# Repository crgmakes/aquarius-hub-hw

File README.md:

# Aquarius Hub Hardware

All the source files for the hub hardware.

# Software 

You will need [KiCad](https://kicad.org) to view and edit this design. Click [here](https://www.kicad.org/download/) to download.

You will also need all the associated libraries and models to drive the design if you want to make changes or view the 3D rendering:

https://github.com/crgmakes/kicad-library.git

Kicad MUST be configured properly to use all the files in this repo. Once you have Kicad installed, under Preferences->Configure Paths..., make the following entries:

1 - KICAD_USER_DIR -> set to the root location of where you placed the above repository.
2 - KICAD_USER_LIBRARY = ${KICAD_USER_DIR}/Library
3 - KICAD_USER_MODEL_DIR = ${KICAD_USER_LIBRARY}/models
4 - KICAD_USER_TEMPLATE_DIR	= ${KICAD_USER_LIBRARY}/templates	

Kicad will operate mostly normally if these are not set properly. You will notice an issue when you view the PCB in 3D mode.

***NOTE***: after makeing a release build in git, if your rendered 3D images are missing components, ensure the path to EVERY component model is set to ${KICAD_USER_MODEL_DIR}/<model name>.

Kicad sometimes replaces the variable with an expansion and that FAILS during the build process because the expanded variable is local and does not match the build environment.

---

THE DESIGN IS PROVIDED "AS IS" AND THE AUTHOR DISCLAIMS ALL WARRANTIES WITH REGARD TO THIS DESIGN INCLUDING ALL IMPLIED WARRANTIES OF MERCHANTABILITY AND FITNESS. IN NO EVENT SHALL THE AUTHOR BE LIABLE FOR ANY SPECIAL, DIRECT, INDIRECT, OR CONSEQUENTIAL DAMAGES OR ANY DAMAGES WHATSOEVER RESULTING FROM LOSS OF USE, DATA OR PROFITS, WHETHER IN AN ACTION OF CONTRACT, NEGLIGENCE OR OTHER TORTIOUS ACTION, ARISING OUT OF OR IN CONNECTION WITH THE USE OR PERFORMANCE OF THIS DESIGN.

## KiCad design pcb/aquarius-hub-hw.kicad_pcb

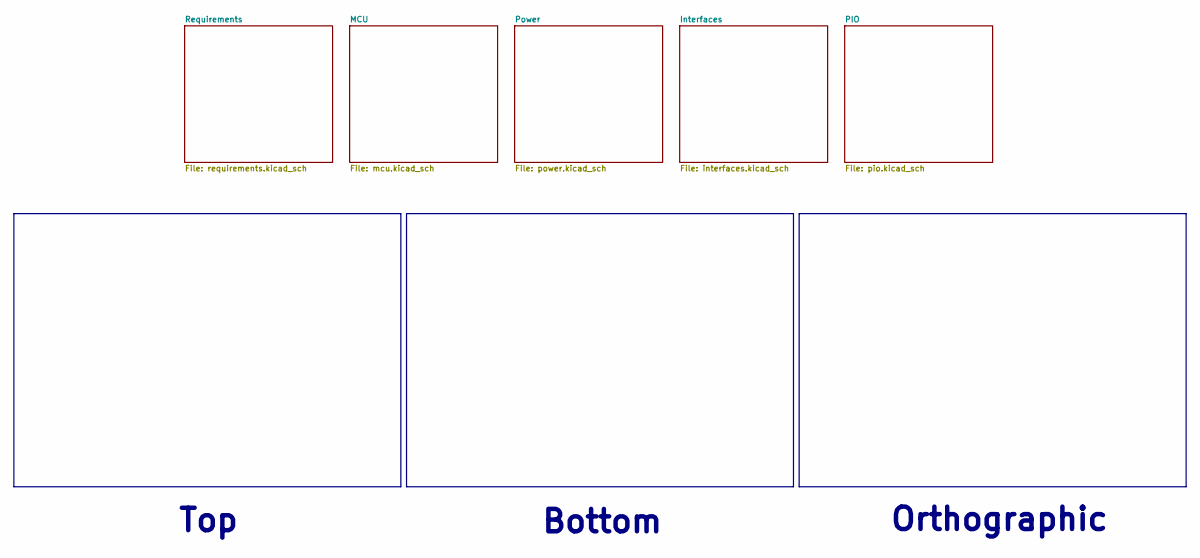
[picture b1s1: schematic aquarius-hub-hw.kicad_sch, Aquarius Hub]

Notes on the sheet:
Orthographic
Top
Bottom

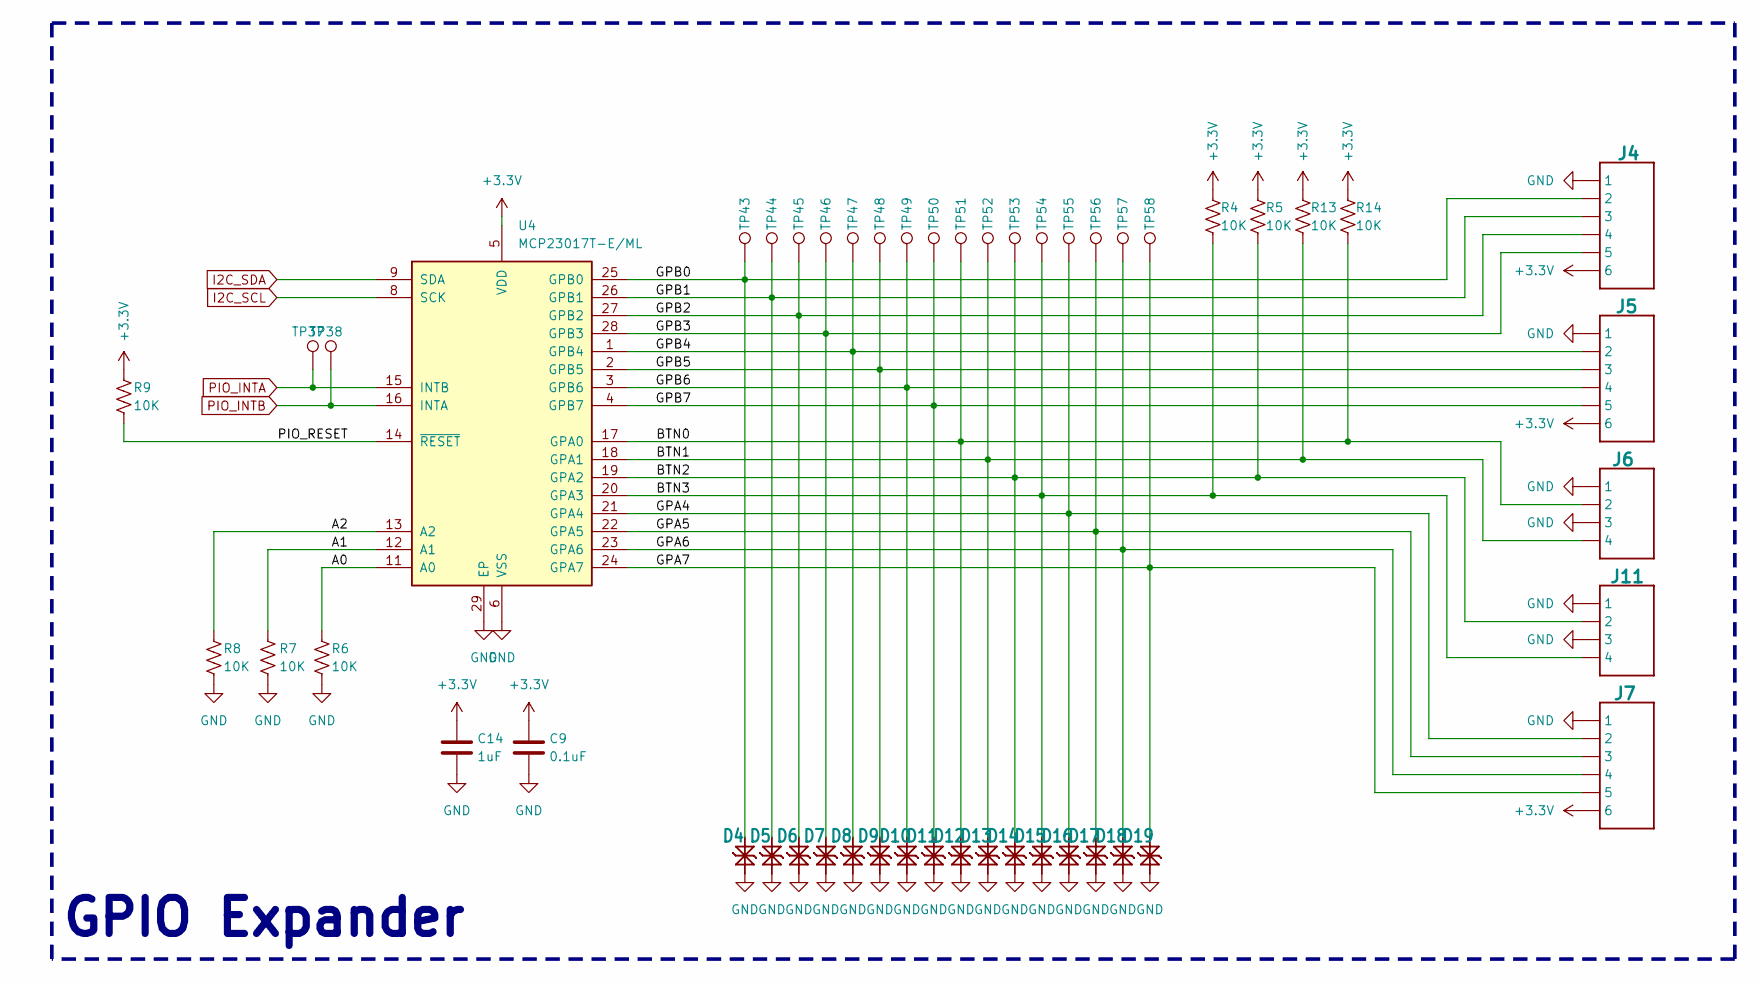
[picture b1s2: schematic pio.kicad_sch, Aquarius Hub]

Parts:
C9: 0.1uF; C_0603_1608Metric; MPN CL10B104KO8NNNC; LCSC C66501
C14: 1uF; C_0603_1608Metric; MPN CGA0603X5R105K160JT; LCSC C6119849
D4, D5, D6, D7, D8, D9, D10, D11, D12, D13, D14, D15, D16, D17, D18, D19: PESD3V3S1BL; DFN1006-2; MPN LESD8D3.3CAT5G; LCSC C5563754
J4, J5, J7: BM06B-SRSS-TB; JST_SH_BM06B-SRSS-TB_1x06-1MP_P1.00mm_Vertical; MPN BM06B-SRSS-TB; LCSC C2845374
J6, J11: BM04B-SRSS-TB; JST_SH_BM04B-SRSS-TB_1x04-1MP_P1.00mm_Vertical; MPN BM04B-SRSS-TBT(LF)(SN); Mouser 306-BM04BSRSSTBTLFSN
R4, R5, R6, R7, R8, R9, R13, R14: 10K; R_0603_1608Metric; MPN FRC0603J103TS; LCSC C2930027
TP37, TP38, TP43, TP44, TP45, TP46, TP47, TP48, TP49, TP50, TP51, TP52, TP53, TP54, TP55, TP56, TP57, TP58: TestPoint_Pad_D1.0mm
U4: MCP23017T-E/ML; QFN-28-1EP_6x6mm_P0.65mm_EP4.25x4.25mm; MPN MCP23017T-E/ML; LCSC C629439

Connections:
+3.3V: C9.1, C14.1, J4.6, J5.6, J7.6, R4.1, R5.1, R9.1, R13.1, R14.1, U4.5 (VDD); also elsewhere on the board
/PIO/A0: R6.1, U4.11 (A0)
/PIO/A1: R7.1, U4.12 (A1)
/PIO/A2: R8.1, U4.13 (A2)
/PIO/BTN0: D12.2 (K2), J6.2, R14.2, TP51.1, U4.17 (GPA0)
/PIO/BTN1: D13.2 (K2), J6.4, R13.2, TP52.1, U4.18 (GPA1)
/PIO/BTN2: D14.2 (K2), J11.2, R5.2, TP53.1, U4.19 (GPA2)
/PIO/BTN3: D15.2 (K2), J11.4, R4.2, TP54.1, U4.20 (GPA3)
/PIO/GPA4: D16.2 (K2), J7.2, TP55.1, U4.21 (GPA4)
/PIO/GPA5: D17.2 (K2), J7.3, TP56.1, U4.22 (GPA5)
/PIO/GPA6: D18.2 (K2), J7.4, TP57.1, U4.23 (GPA6)
/PIO/GPA7: D19.2 (K2), J7.5, TP58.1, U4.24 (GPA7)
/PIO/GPB0: D4.2 (K2), J4.2, TP43.1, U4.25 (GPB0)
/PIO/GPB1: D5.2 (K2), J4.3, TP44.1, U4.26 (GPB1)
/PIO/GPB2: D6.2 (K2), J4.4, TP45.1, U4.27 (GPB2)
/PIO/GPB3: D7.2 (K2), J4.5, TP46.1, U4.28 (GPB3)
/PIO/GPB4: D8.2 (K2), J5.2, TP47.1, U4.1 (GPB4)
/PIO/GPB5: D9.2 (K2), J5.3, TP48.1, U4.2 (GPB5)
/PIO/GPB6: D10.2 (K2), J5.4, TP49.1, U4.3 (GPB6)
/PIO/GPB7: D11.2 (K2), J5.5, TP50.1, U4.4 (GPB7)
/PIO/PIO_RESET: R9.2, U4.14 (~RESET)
GND: C9.2, C14.2, D4.1 (K1), D5.1 (K1), D6.1 (K1), D7.1 (K1), D8.1 (K1), D9.1 (K1), D10.1 (K1), D11.1 (K1), D12.1 (K1), D13.1 (K1), D14.1 (K1), D15.1 (K1), D16.1 (K1), D17.1 (K1), D18.1 (K1), D19.1 (K1), J4.1, J5.1, J6.1, J6.3, J7.1, J11.1, J11.3, R6.2, R7.2, R8.2, U4.6 (VSS), U4.29 (EP); also elsewhere on the board
I2C_SCL: U4.8 (SCK); also elsewhere on the board
I2C_SDA: U4.9 (SDA); also elsewhere on the board
PIO_INTA: TP37.1, U4.15 (INTB); also elsewhere on the board
PIO_INTB: TP38.1, U4.16 (INTA); also elsewhere on the board

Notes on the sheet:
GPIO Expander

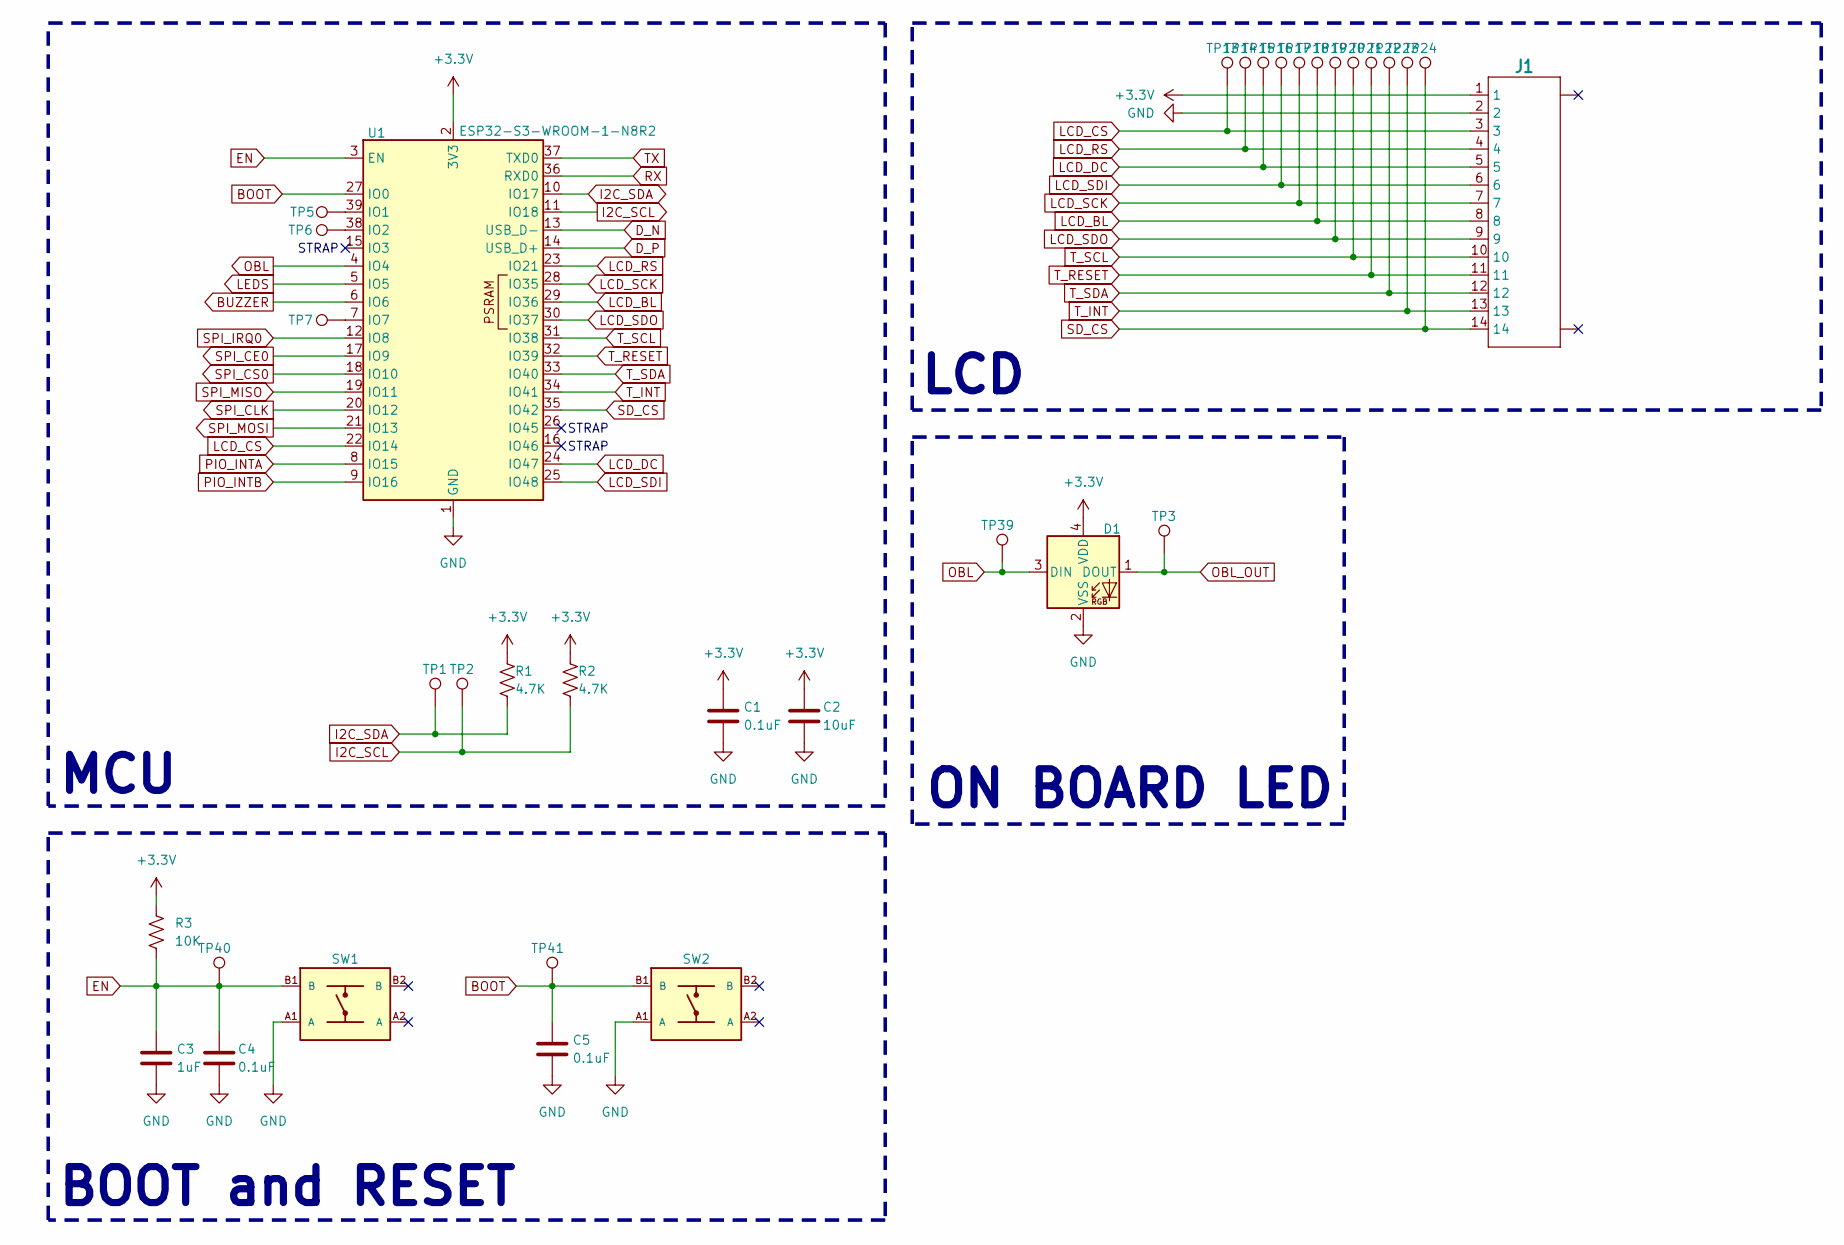
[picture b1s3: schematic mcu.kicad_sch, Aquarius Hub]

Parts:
C1, C4: 0.1uF; C_0603_1608Metric; MPN CL10B104KO8NNNC; Mouser 187-CL10B104KO8NNNC
C2: 10uF; C_0603_1608Metric; MPN CL10A106MO8NQNC; Mouser 187-CL10A106MO8NQNC
C3: 1uF; C_0603_1608Metric; Tolerance 10%; MPN CGA0603X5R105K160JT; Mouser 187-CL10B105KO8NNNC
C5: 0.1uF; C_0603_1608Metric; MPN CL10B104KO8NNNC; Digikey 1276-1005-2-ND
D1: WS2812B-2020; LED_WS2812B-2020_PLCC4_2.0x2.0mm; MPN WS2812C-2020-V1; LCSC C2976072
J1: XF2M-1415-1A; MPN XF2M-1415-1A; Mouser 653-XF2M-1415-1A
R1, R2: 4.7K; R_0603_1608Metric; MPN FRC0603J472 TS; Mouser 652-CR0603-JW-472ELF
R3: 10K; R_0603_1608Metric; MPN FRC0603J103TS; Mouser 652-CR0603-JW-103ELF
SW1, SW2: EVQ-Q2B02W; MPN EVQ-Q2B02W; Mouser 667-EVQ-Q2B02W
TP1, TP2, TP3, TP5, TP6, TP7, TP13, TP14, TP15, TP16, TP17, TP18, TP19, TP20, TP21, TP22, TP23, TP24, TP39, TP40, TP41: TestPoint_Pad_D1.0mm
U1: ESP32-S3-WROOM-1-N8R2; MPN ESP32-S3-WROOM-1-N8R2; Mouser 356-ESP32-S3WRM1N8R2

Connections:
+3.3V: C1.1, C2.1, D1.4 (VDD), J1.1, R1.1, R2.1, R3.1, U1.2 (3V3); also elsewhere on the board
BOOT: C5.1, SW2.B1 (B), TP41.1, U1.27 (IO0)
BUZZER: U1.6 (IO6); also elsewhere on the board
D_N: U1.13 (USB_D-); also elsewhere on the board
D_P: U1.14 (USB_D+); also elsewhere on the board
EN: C3.1, C4.1, R3.2, SW1.B1 (B), TP40.1, U1.3 (EN)
GND: C1.2, C2.2, C3.2, C4.2, C5.2, D1.2 (VSS), J1.2, SW1.A1 (A), SW2.A1 (A), U1.1 (GND), U1.40 (GND), U1.41 (GND); also elsewhere on the board
I2C_SCL: R2.2, TP2.1, U1.11 (IO18); also elsewhere on the board
I2C_SDA: R1.2, TP1.1, U1.10 (IO17); also elsewhere on the board
LCD_BL: J1.8, TP18.1, U1.29 (IO36)
LCD_CS: J1.3, TP13.1, U1.22 (IO14)
LCD_DC: J1.5, TP15.1, U1.24 (IO47)
LCD_RS: J1.4, TP14.1, U1.23 (IO21)
LCD_SCK: J1.7, TP17.1, U1.28 (IO35)
LCD_SDI: J1.6, TP16.1, U1.25 (IO48)
LCD_SDO: J1.9, TP19.1, U1.30 (IO37)
LEDS: U1.5 (IO5); also elsewhere on the board
unnamed: TP5.1, U1.39 (IO1)
unnamed: TP6.1, U1.38 (IO2)
unnamed: TP7.1, U1.7 (IO7)
OBL: D1.3 (DIN), TP39.1, U1.4 (IO4)
OBL_OUT: D1.1 (DOUT), TP3.1
PIO_INTA: U1.8 (IO15); also elsewhere on the board
PIO_INTB: U1.9 (IO16); also elsewhere on the board
RX: U1.36 (RXD0); also elsewhere on the board
SD_CS: J1.14, TP24.1, U1.35 (IO42)
SPI_CE0: U1.17 (IO9); also elsewhere on the board
SPI_CLK: U1.20 (IO12); also elsewhere on the board
SPI_CS0: U1.18 (IO10); also elsewhere on the board
SPI_IRQ0: U1.12 (IO8); also elsewhere on the board
SPI_MISO: U1.19 (IO11); also elsewhere on the board
SPI_MOSI: U1.21 (IO13); also elsewhere on the board
TX: U1.37 (TXD0); also elsewhere on the board
T_INT: J1.13, TP23.1, U1.34 (IO41)
T_RESET: J1.11, TP21.1, U1.32 (IO39)
T_SCL: J1.10, TP20.1, U1.31 (IO38)
T_SDA: J1.12, TP22.1, U1.33 (IO40)

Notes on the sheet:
MCU
STRAP
BOOT and RESET
ON BOARD LED
LCD

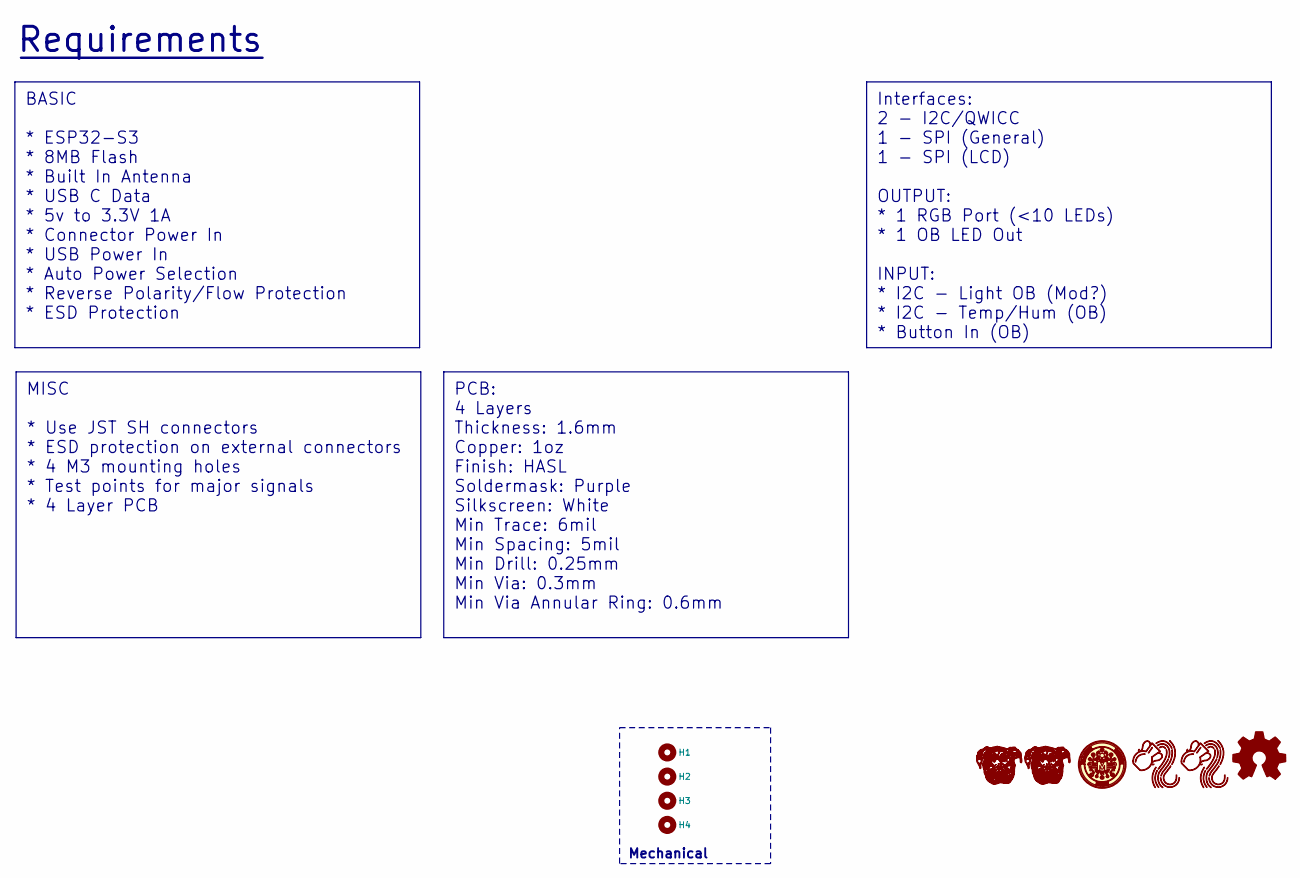
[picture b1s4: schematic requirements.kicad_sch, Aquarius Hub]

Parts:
H1, H2, H3, H4: MountingHole_3.2mm_M3_Pad_Via
LOGO1: CRGM Logo 5mm
LOGO2: Aquarius Logo 10mm
LOGO3: OSHW-Logo_5.7x6mm_SilkScreen
LOGO4: Aquarius Logo 5mm
LOGO5, LOGO6: Roxy 5mm

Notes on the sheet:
Mechanical
Requirements
BASIC * ESP32-S3 * 8MB Flash * Built In Antenna * USB C Data * 5v to 3.3V 1A * Connector Power In * USB Power In * Auto Power Selection * Reverse Polarity/Flow Protection * ESD Protection
MISC * Use JST SH connectors * ESD protection on external connectors * 4 M3 mounting holes * Test points for major signals * 4 Layer PCB
PCB: 4 Layers Thickness: 1.6mm Copper: 1oz Finish: HASL Soldermask: Purple Silkscreen: White Min Trace: 6mil Min Spacing: 5mil Min Drill: 0.25mm Min Via: 0.3mm Min Via Annular Ring: 0.6mm
Interfaces: 2 - I2C/QWICC 1 - SPI (General) 1 - SPI (LCD) OUTPUT: * 1 RGB Port (<10 LEDs) * 1 OB LED Out INPUT: * I2C - Light OB (Mod?) * I2C - Temp/Hum (OB) * Button In (OB)

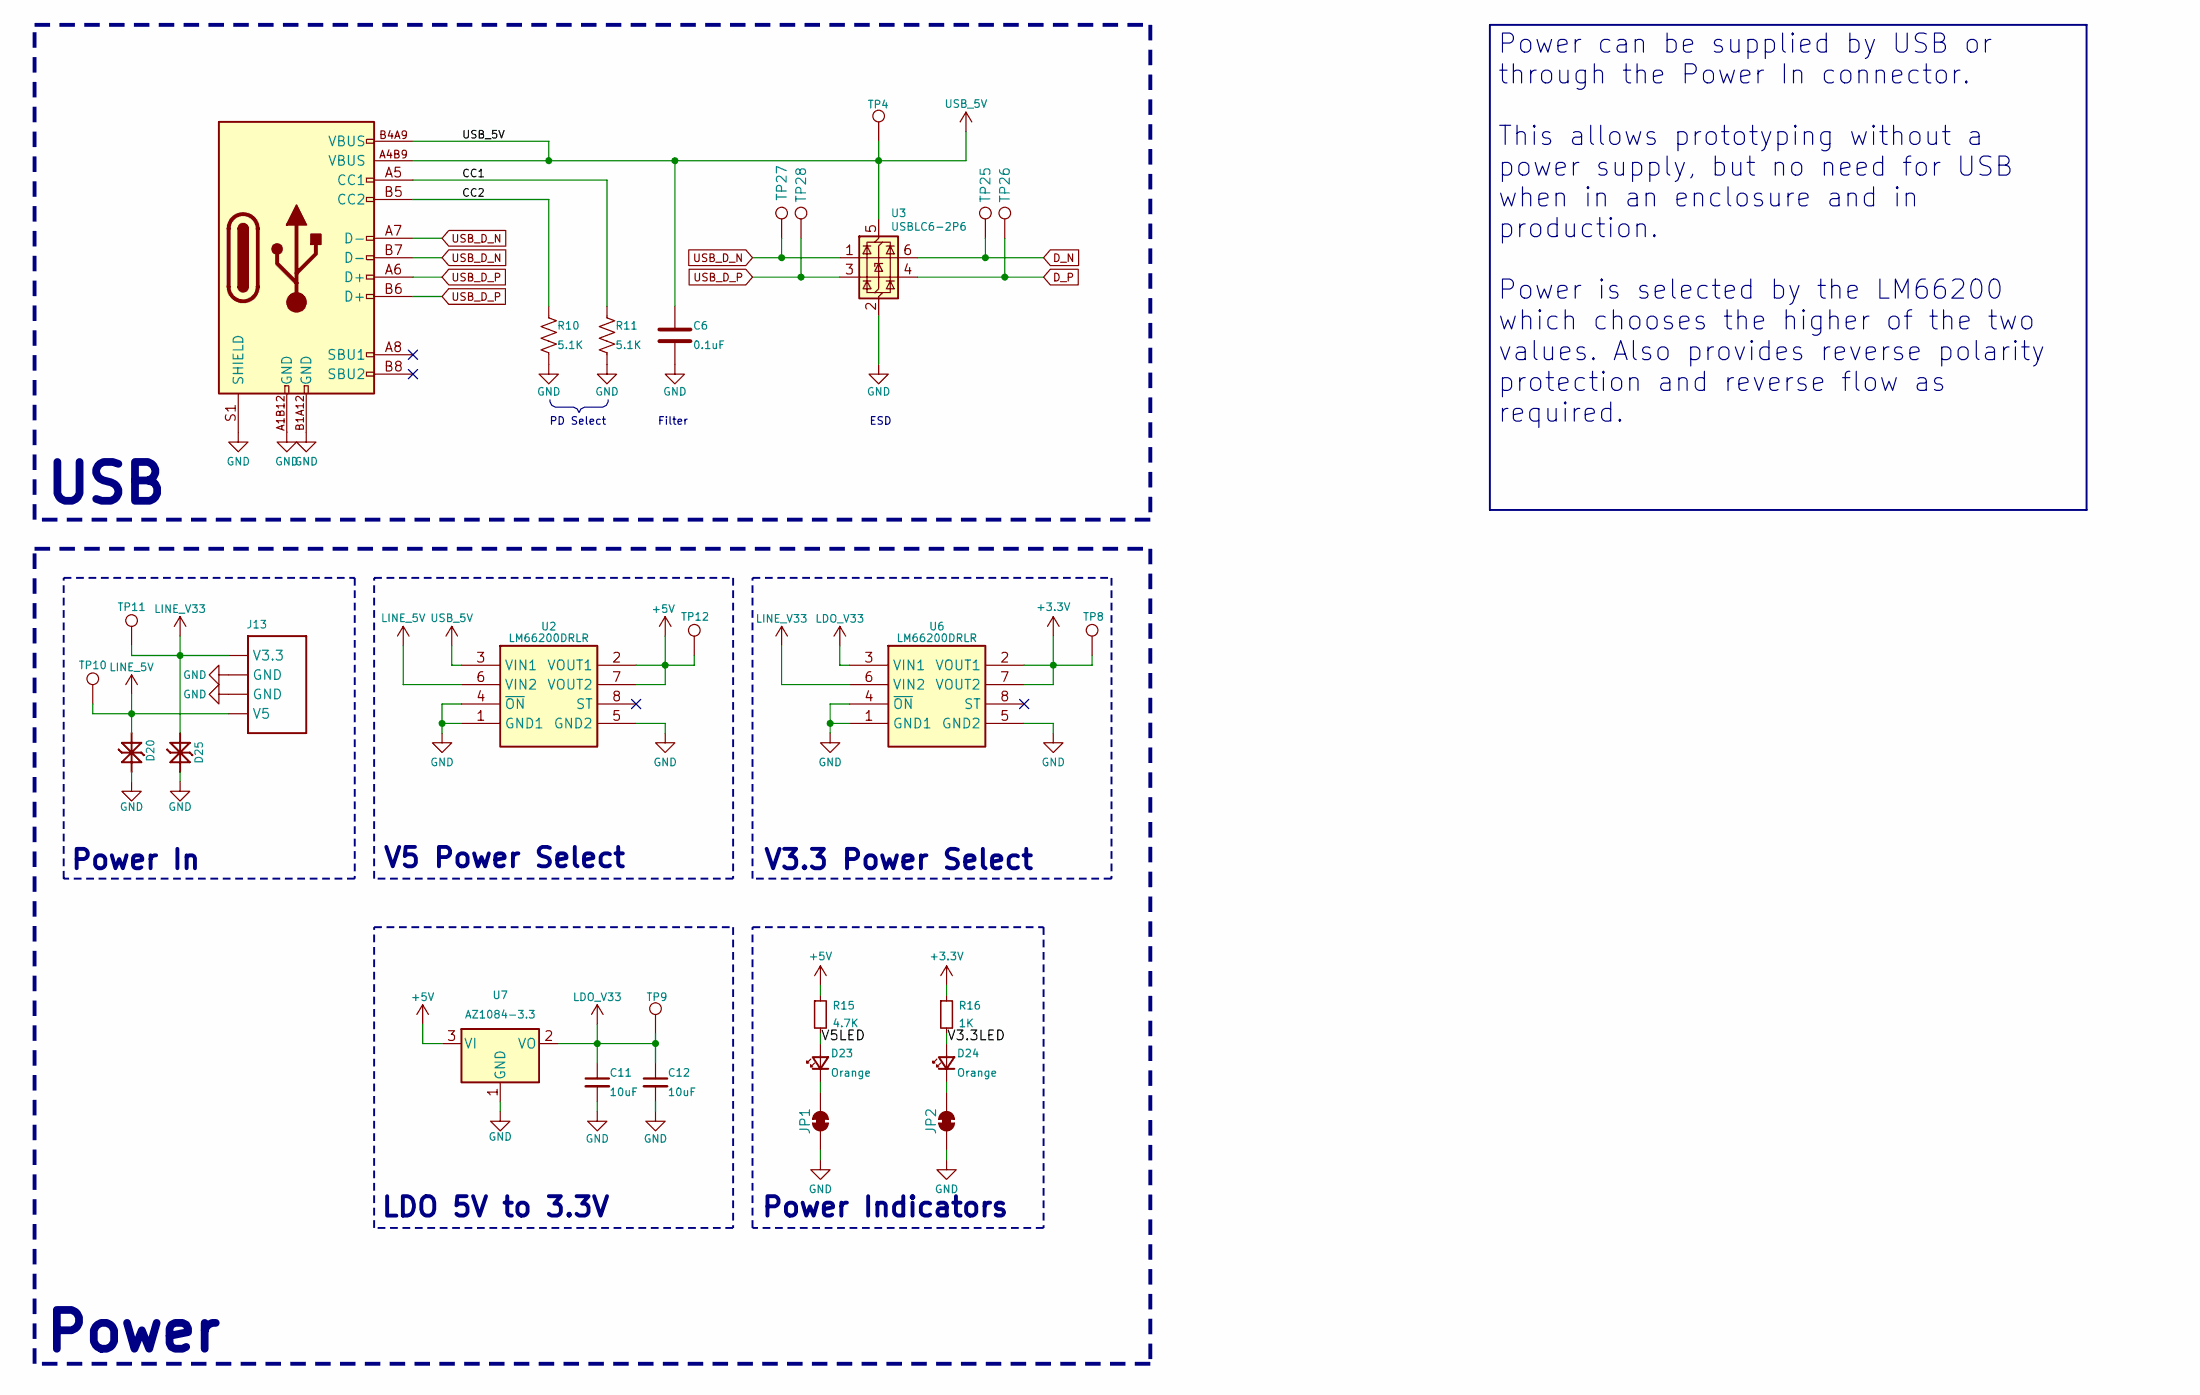
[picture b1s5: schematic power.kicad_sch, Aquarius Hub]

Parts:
C6: 0.1uF; C_0603_1608Metric; MPN CL10B104KO8NNNC; LCSC C66501
C11, C12: 10uF; C_0603_1608Metric; MPN CL10A106MO8NQNC; Mouser 187-CL10A106MO8NQNC
D20: PESD5V5C1BL; DFN1006-2; MPN PESD5V5C1BLYL; LCSC C2827636
D23, D24: Orange; LED_0603_1608Metric; MPN XL-1608UOC-06; Mouser 859-LTST-C190KFKT
D25: PESD3V3S1BL; DFN1006-2; MPN LESD8D3.3CAT5G; LCSC C5563754
J2: USB_C_USB2.0_16P; GCT_USB4105-GF-A; MPN USB4105-GF-A-060; Mouser 640-USB4105-GF-A-060
J13: SM04B-SRSS-TB; JST_SH_SM04B-SRSS-TB_1x04-1MP_P1.00mm_Horizontal; MPN SM04B-SRSS-TBT(LF)(SN); LCSC C2763614
JP1, JP2: SolderJumper-2_P1.3mm_Bridged_RoundedPad1.0x1.5mm
R10, R11: 5.1K; R_0603_1608Metric; MPN FRC0603J512 TS; Mouser 652-CR0603JW-512ELF
R15: 4.7K; R_0603_1608Metric; MPN FRC0603J472 TS; Mouser 652-CR0603-JW-472ELF
R16: 1K; R_0603_1608Metric; MPN FRC0603J102 TS; Mouser 652-CR0603-JW-102ELF
TP4, TP8, TP9, TP10, TP11, TP12, TP25, TP26, TP27, TP28: TestPoint_Pad_D1.0mm
U2, U6: LM66200DRLR; SOTFL50P160X60-8N; MPN LM66200DRLR; Mouser 595-LM66200DRLR
U3: USBLC6-2P6; SOT-666; MPN USBLC6-2P6; LCSC C2827693
U7: AZ1084-3.3; TO-252-2; MPN AZ1084CD-3.3TRG1; Mouser 621-AZ1084CD-3.3TRG1

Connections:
+3.3V: R16.1, TP8.1, U6.2 (VOUT1), U6.7 (VOUT2); also elsewhere on the board
+5V: R15.1, TP12.1, U2.2 (VOUT1), U2.7 (VOUT2), U7.3 (VI)
/Power/CC1: J2.A5 (CC1), R11.1
/Power/CC2: J2.B5 (CC2), R10.1
/Power/V3.3LED: D24.2 (A), R16.2
/Power/V5LED: D23.2 (A), R15.2
D_N: TP25.1, U3.6 (I/O1); also elsewhere on the board
D_P: TP26.1, U3.4 (I/O2); also elsewhere on the board
GND: C6.2, C11.2, C12.2, D20.1 (K1), D25.1 (K1), J2.A1B12 (GND), J2.B1A12 (GND), J2.S1 (SHIELD), J13.2 (GND), J13.3 (GND), JP1.1 (A), JP2.1 (A), R10.2, R11.2, U2.1 (GND1), U2.4 (~ON), U2.5 (GND2), U3.2 (GND), U6.1 (GND1), U6.4 (~ON), U6.5 (GND2), U7.1 (GND); also elsewhere on the board
LDO_V33: C11.1, C12.1, TP9.1, U6.3 (VIN1), U7.2 (VO)
LINE_5V: D20.2 (K2), J13.1 (V5), TP10.1, U2.6 (VIN2)
LINE_V33: D25.2 (K2), J13.4 (V3.3), TP11.1, U6.6 (VIN2)
unnamed: D23.1 (K), JP1.2 (B)
unnamed: D24.1 (K), JP2.2 (B)
USB_5V: C6.1, J2.A4B9 (VBUS), J2.B4A9 (VBUS), TP4.1, U2.3 (VIN1), U3.5 (VBUS)
USB_D_N: J2.A7 (D-), J2.B7 (D-), TP27.1, U3.1 (I/O1)
USB_D_P: J2.A6 (D+), J2.B6 (D+), TP28.1, U3.3 (I/O2)

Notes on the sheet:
Power Indicators
V3.3 Power Select
Power In
USB
Filter
PD Select
LDO 5V to 3.3V
ESD
V5 Power Select
Power
Power can be supplied by USB or through the Power In connector. This allows prototyping without a power supply, but no need for USB when in an enclosure and in production. Power is selected by the LM66200 which chooses the higher of the two values. Also provides reverse polarity protection and reve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

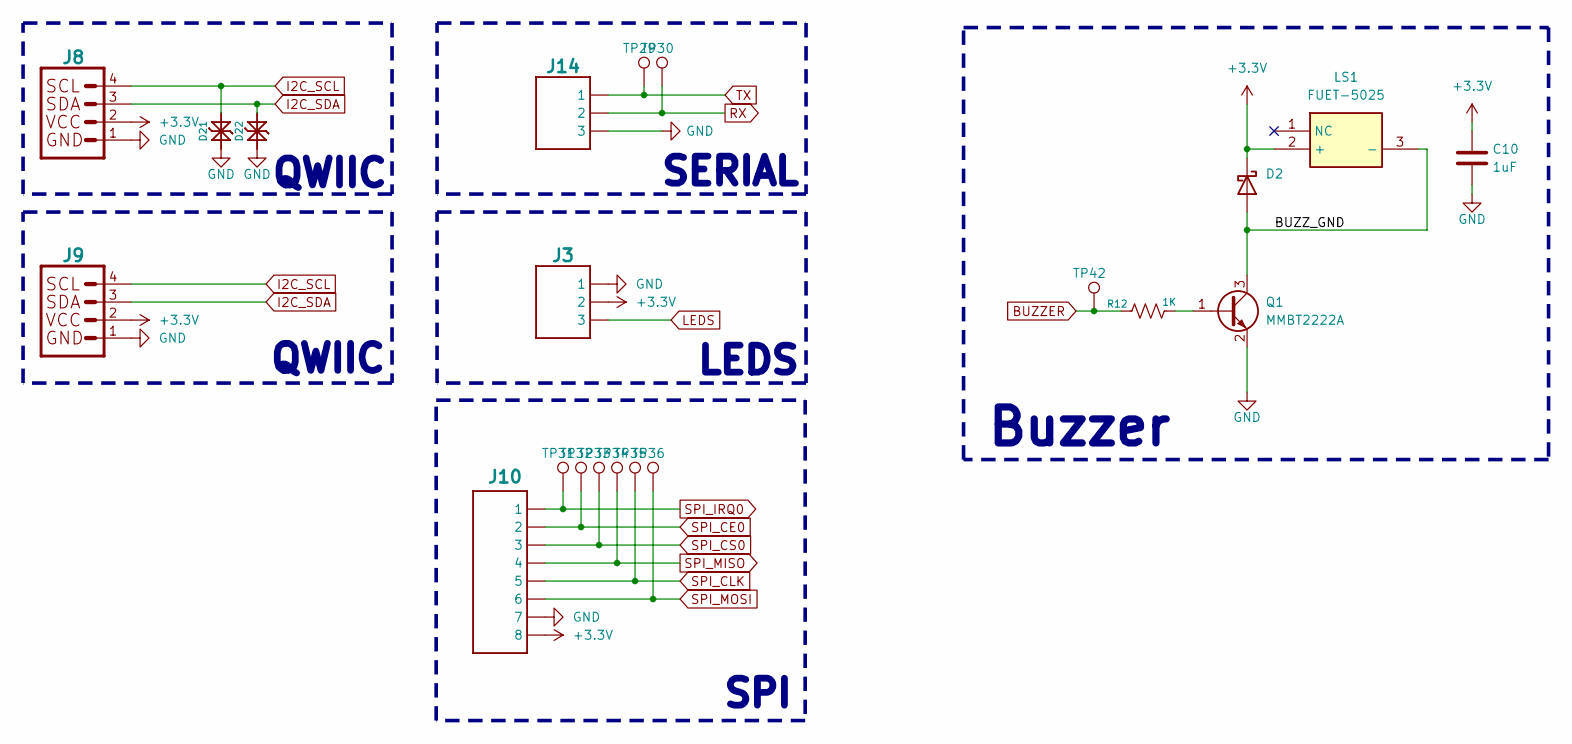
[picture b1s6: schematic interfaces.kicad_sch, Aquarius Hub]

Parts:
C10: 1uF; C_0603_1608Metric; MPN CGA0603X5R105K160JT; LCSC C6119849
D2: D_Schottky; D_SOD-523; MPN MSK4010; LCSC C345958
D21, D22: PESD3V3S1BL; DFN1006-2; MPN LESD8D3.3CAT5G; LCSC C5563754
J3, J14: BM03B-SRSS-TB; JST_SH_BM03B-SRSS-TB_1x03-1MP_P1.00mm_Vertical; MPN BM03B-SRSS-TB; LCSC C2919600
J8, J9: BM04B-SRSS-TB; JST_SH_BM04B-SRSS-TB_1x04-1MP_P1.00mm_Vertical; MPN BM04B-SRSS-TB; LCSC C2919601
J10: BM08B-SRSS-TB; JST_SH_BM08B-SRSS-TB_1x08-1MP_P1.00mm_Vertical; MPN BM08B-SRSS-TB(LF)(SN); LCSC C2845376
LS1: FUET-5025; MPN FUET-5025; Mouser 490-CMT-0502-75SMTTR
Q1: MMBT2222A; SOT-523; MPN MMBT2222AT-7-F; Mouser 621-MMBT2222AT-F
R12: 1K; R_0603_1608Metric; MPN FRC0603J102 TS; LCSC C2907113
TP29, TP30, TP31, TP32, TP33, TP34, TP35, TP36, TP42: TestPoint_Pad_D1.0mm

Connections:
+3.3V: C10.1, D2.1 (K), J3.2, J8.2, J9.2, J10.8, LS1.2 (+); also elsewhere on the board
/Interfaces/BUZZ_GND: D2.2 (A), LS1.3 (-), Q1.3 (C)
BUZZER: R12.1, TP42.1; also elsewhere on the board
GND: C10.2, D21.1 (K1), D22.1 (K1), J3.1, J8.1, J9.1, J10.7, J14.3, Q1.2 (E); also elsewhere on the board
I2C_SCL: D21.2 (K2), J8.4, J9.4; also elsewhere on the board
I2C_SDA: D22.2 (K2), J8.3, J9.3; also elsewhere on the board
LEDS: J3.3; also elsewhere on the board
unnamed: Q1.1 (B), R12.2
RX: J14.2, TP30.1; also elsewhere on the board
SPI_CE0: J10.2, TP32.1; also elsewhere on the board
SPI_CLK: J10.5, TP35.1; also elsewhere on the board
SPI_CS0: J10.3, TP33.1; also elsewhere on the board
SPI_IRQ0: J10.1, TP31.1; also elsewhere on the board
SPI_MISO: J10.4, TP34.1; also elsewhere on the board
SPI_MOSI: J10.6, TP36.1; also elsewhere on the board
TX: J14.1, TP29.1; also elsewhere on the board

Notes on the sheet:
LEDS
QWIIC
Buzzer
SERIAL
SPI

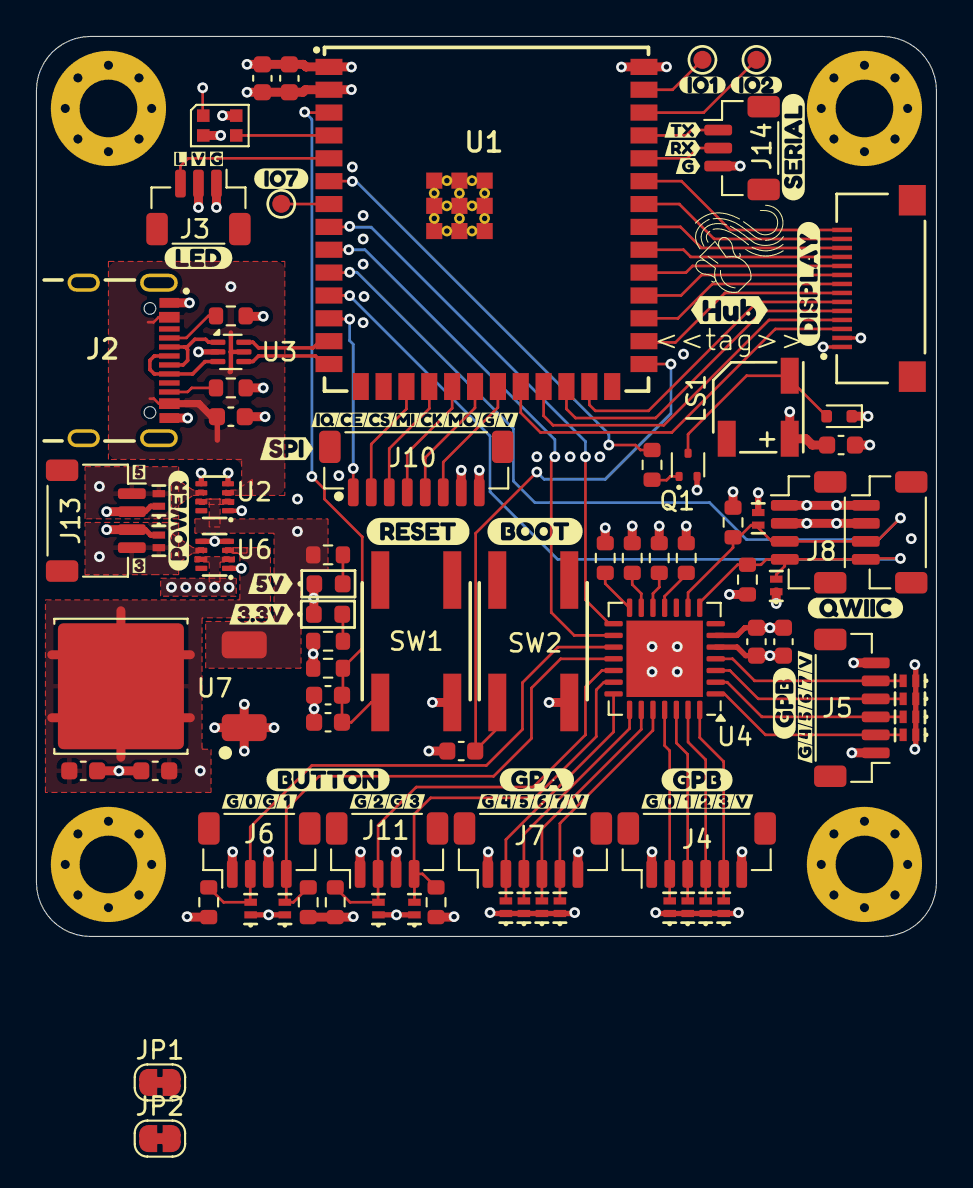
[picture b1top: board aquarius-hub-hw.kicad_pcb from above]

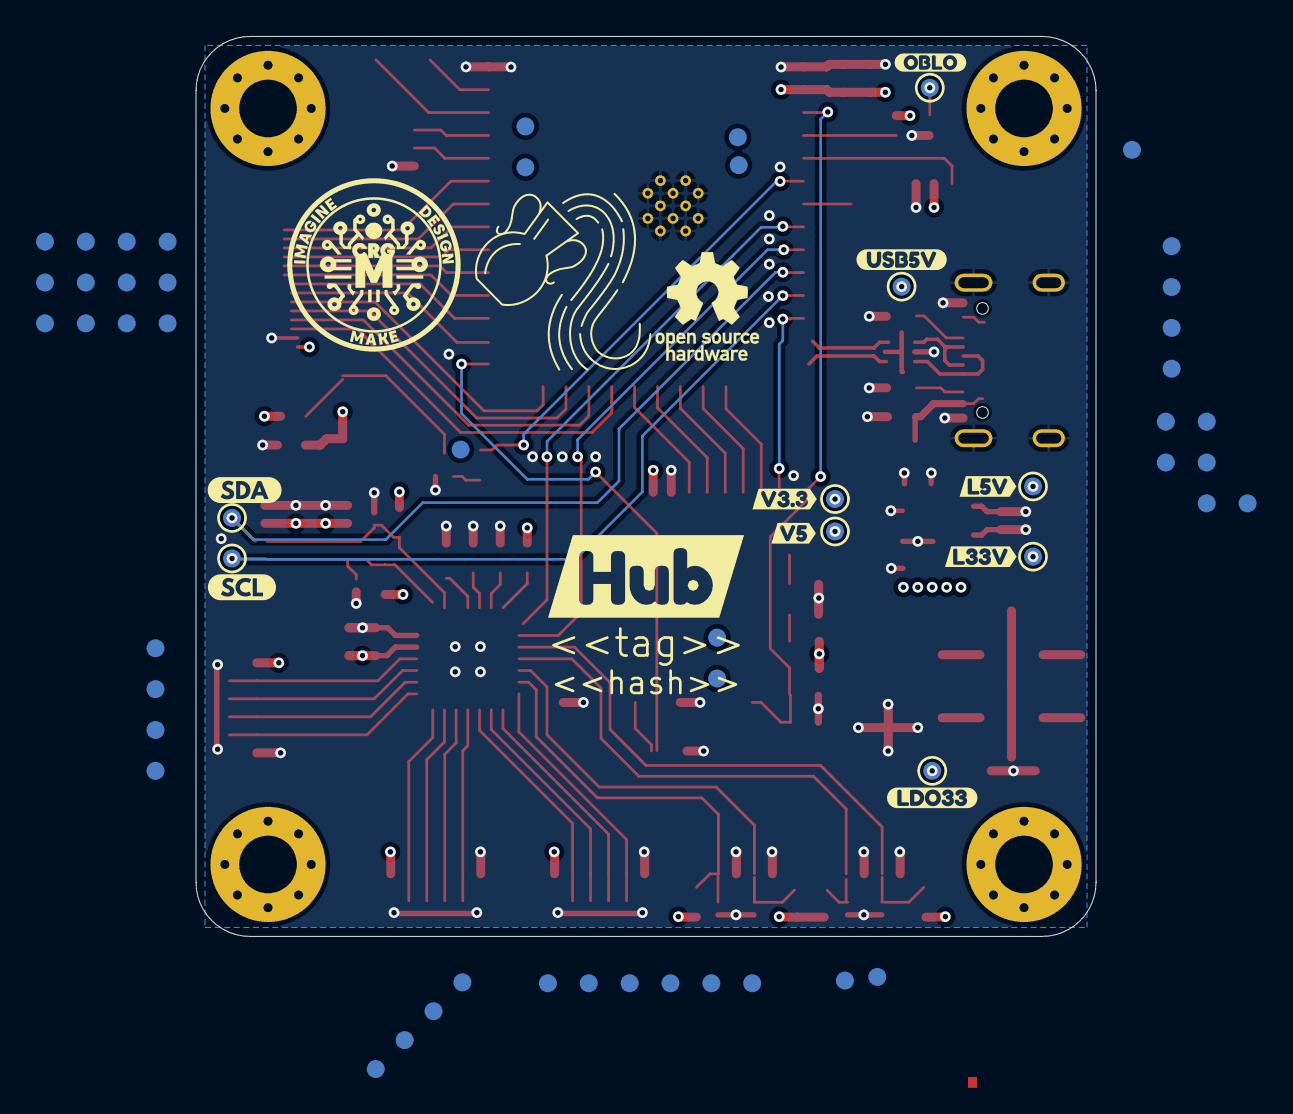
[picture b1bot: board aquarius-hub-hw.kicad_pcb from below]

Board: 4 copper layers, 50.0 x 50.0 mm, 212 parts (68 on the bottom side), 72 nets.

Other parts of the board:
kibuzzard-67B9F9C2: G***; kibuzzard-67B9F9C2
kibuzzard-67B9F9CD: G***; kibuzzard-67B9F9CD
kibuzzard-680D06A5: G***; kibuzzard-680D06A5
kibuzzard-680D069E: G***; kibuzzard-680D069E
kibuzzard-680D0262: G***; kibuzzard-680D0262
kibuzzard-683B54B0: G***; kibuzzard-683B54B0
kibuzzard-683B594D: G***; kibuzzard-683B594D
kibuzzard-683B5370: G***; kibuzzard-683B5370
kibuzzard-683B5376: G***; kibuzzard-683B5376
kibuzzard-683C500B: G***; kibuzzard-683C500B
kibuzzard-683C5017: G***; kibuzzard-683C5017
kibuzzard-689E525E: G***; kibuzzard-689E525E
kibuzzard-689E5275: G***; kibuzzard-689E5275
kibuzzard-6812E3A0: G***; kibuzzard-6812E3A0
kibuzzard-6812E3AD: G***; kibuzzard-6812E3AD
kibuzzard-6812E3BB: G***; kibuzzard-6812E3BB
kibuzzard-6812E3C5: G***; kibuzzard-6812E3C5
kibuzzard-6812E37E: G***; kibuzzard-6812E37E
kibuzzard-6812E420: G***; kibuzzard-6812E420
kibuzzard-68153CC4, kibuzzard-68153CC4#2, kibuzzard-68153CC4#3: G***; kibuzzard-68153CC4
kibuzzard-68153CC9: G***; kibuzzard-68153CC9
kibuzzard-68153CCE: G***; kibuzzard-68153CCE
kibuzzard-68153CDD: G***; kibuzzard-68153CDD
kibuzzard-68153CE4: G***; kibuzzard-68153CE4
kibuzzard-68153CEB: G***; kibuzzard-68153CEB
kibuzzard-68153CEF: G***; kibuzzard-68153CEF
kibuzzard-68194F3F: G***; kibuzzard-68194F3F
kibuzzard-68194F50: G***; kibuzzard-68194F50
kibuzzard-68366CAF: G***; kibuzzard-68366CAF
kibuzzard-68574A7C: G***; kibuzzard-68574A7C
kibuzzard-68574A8F: G***; kibuzzard-68574A8F
kibuzzard-68574A9F: G***; kibuzzard-68574A9F
kibuzzard-68574AC2: G***; kibuzzard-68574AC2
kibuzzard-68574AD3: G***; kibuzzard-68574AD3
kibuzzard-68574B95: G***; kibuzzard-68574B95
kibuzzard-68574D7F: G***; kibuzzard-68574D7F
kibuzzard-68574D8A: G***; kibuzzard-68574D8A
kibuzzard-68574D75: G***; kibuzzard-68574D75
kibuzzard-68574D94: G***; kibuzzard-68574D94
kibuzzard-681420CD: G***; kibuzzard-681420CD
kibuzzard-681420D1: G***; kibuzzard-681420D1
kibuzzard-681420D5: G***; kibuzzard-681420D5
kibuzzard-681420DA, kibuzzard-681420DA#2: G***; kibuzzard-681420DA
kibuzzard-681420E9: G***; kibuzzard-681420E9
kibuzzard-681420F3: G***; kibuzzard-681420F3
kibuzzard-681421A1: G***; kibuzzard-681421A1
kibuzzard-681421A9: G***; kibuzzard-681421A9
kibuzzard-683921F2: G***; kibuzzard-683921F2
kibuzzard-6810346D: G***; kibuzzard-6810346D
kibuzzard-6810349E: G***; kibuzzard-6810349E
kibuzzard-6814204F, kibuzzard-6814204F#2: G***; kibuzzard-6814204F
kibuzzard-6814212B: G***; kibuzzard-6814212B
kibuzzard-6815408B: G***; kibuzzard-6815408B
kibuzzard-6857318D: G***; kibuzzard-6857318D
kibuzzard-68142030, kibuzzard-68142030#2: G***; kibuzzard-68142030
kibuzzard-68142039, kibuzzard-68142039#2: G***; kibuzzard-68142039
kibuzzard-68142043, kibuzzard-68142043#2: G***; kibuzzard-68142043
kibuzzard-68142110: G***; kibuzzard-68142110
kibuzzard-68142199: G***; kibuzzard-68142199
kibuzzard-68154095, kibuzzard-68154095#2, kibuzzard-68154095#3: G***; kibuzzard-68154095
kibuzzard-68392226: G***; kibuzzard-68392226
